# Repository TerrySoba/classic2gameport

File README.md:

Classic2Gameport
================

About
-----
Classic2Gameport is an adapter that allows to connect up to two [Nintendo Wii Classic Controllers](https://en.wikipedia.org/wiki/Classic_Controller) to [PC Gameports](https://en.wikipedia.org/wiki/Game_port).
The adapter acts like a Gravis Gamepad.

Supported Devices
-----------------

The following Nintendo controllers are supported:
 * Classic Controller
 * Classic Controler Pro
 * SNES Mini Controller

The PC needs to have a Gameport to use this adapter.

Adapter Modes
-------------

| Mode | Combination | Description |
|------|-------------|--|
| Normal Mode | SELECT + DOWN | Button B -> 1<br>Button Y -> 2<br>Button A -> 3<br>Button X -> 4 |
| Two Player Mode | (connect two controllers) | Button B1 -> 1<br>Button Y1 -> 2<br>Button B2 -> 3<br>Button Y2 -> 4<br>
| Jump'n'Run Mode | SELECT + UP | Button Y -> 1<br>Button A -> 2<br>Button B -> Up |

Building Instructions
---------------------

Here are some images of the assembled adapter:

The Kicad files of the PCB can be found in the pcb directory of the repository.

The firmware for the ST STM32G071KxT microcontroller can be found in the firmware directory.

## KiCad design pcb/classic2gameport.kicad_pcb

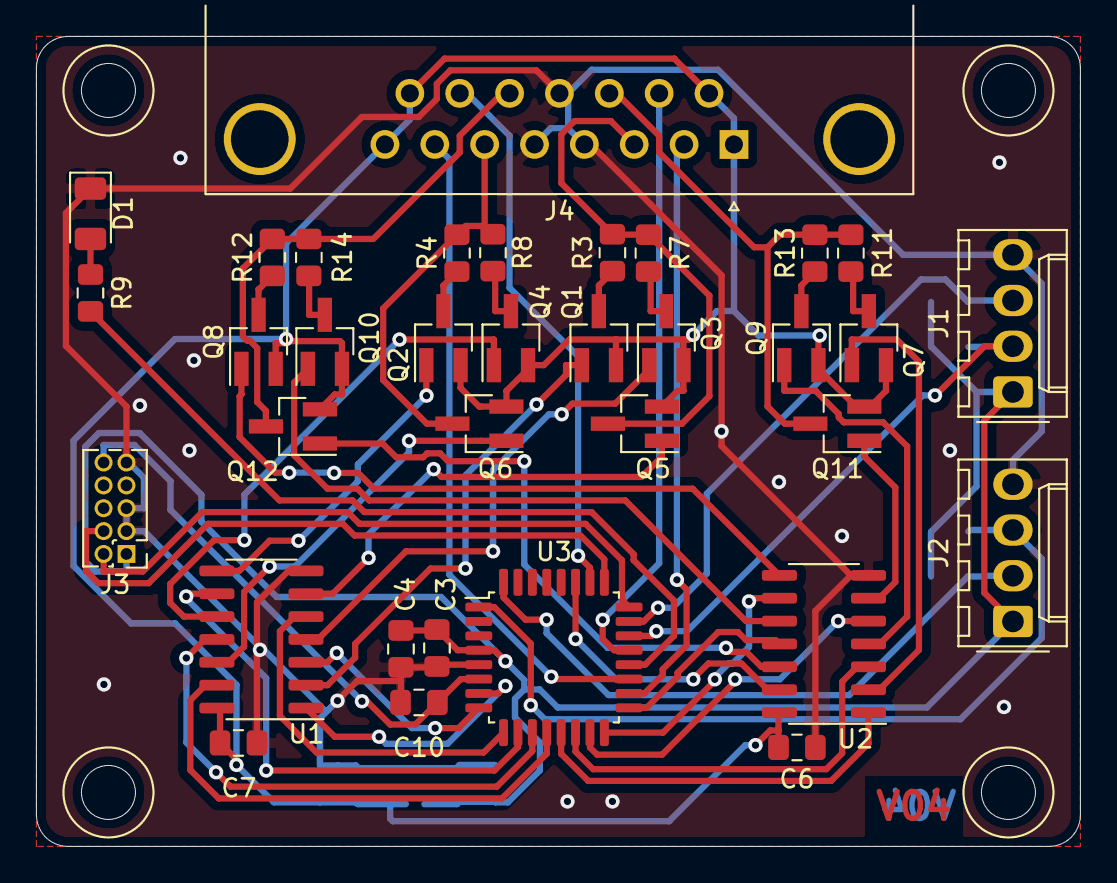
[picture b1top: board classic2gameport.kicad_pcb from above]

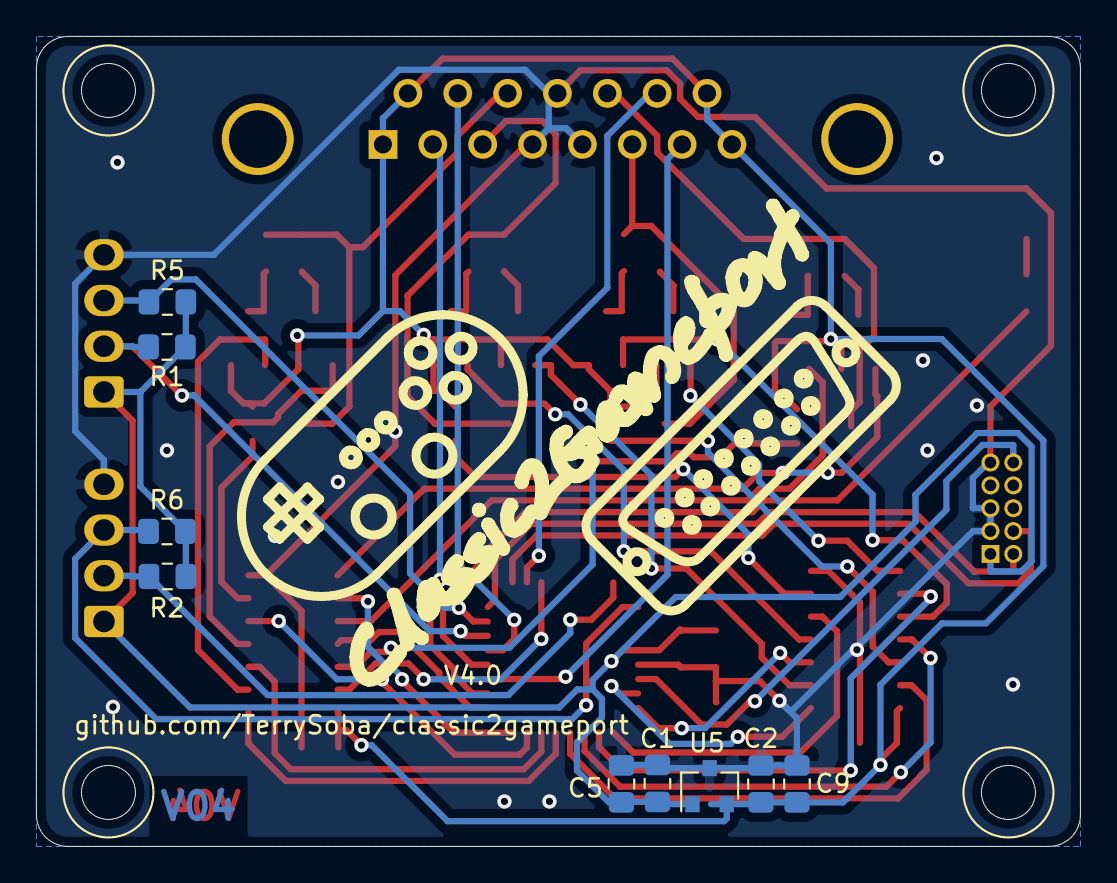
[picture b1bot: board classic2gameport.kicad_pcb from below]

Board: 2 copper layers, 58.0 x 45.0 mm, 43 parts (9 on the bottom side), 52 nets.

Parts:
C1, C2, C3, C6, C7, C10: 100nF; C_0805_2012Metric_Pad1.15x1.40mm_HandSolder
C4: 1µF; C_0805_2012Metric_Pad1.15x1.40mm_HandSolder
C5, C9: 4.7µF; C_0805_2012Metric_Pad1.15x1.40mm_HandSolder
D1: LED; LED_1206_3216Metric
J1, J2: Conn_01x04; Molex_KK-254_AE-6410-04A_1x04_P2.54mm_Vertical
J3: Conn_02x05_Odd_Even; PinHeader_2x05_P1.27mm_Vertical
J4: DB15_Male; DSUB-15_Male_Horizontal_P2.77x2.84mm_EdgePinOffset4.94mm_Ho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
Q1, Q2, Q3, Q4, Q5, Q6, Q7, Q8, Q9, Q10, Q11, Q12: Q_PMOS_GSD; SOT-23_Handsoldering
R1, R2, R5, R6: 1kR; R_0805_2012Metric_Pad1.15x1.40mm_HandSolder
R3, R4, R7, R8, R11, R12, R13, R14: 100kR; R_0805_2012Metric_Pad1.15x1.40mm_HandSolder
R9: 470R; R_0805_2012Metric_Pad1.15x1.40mm_HandSolder
U1, U2: 74HC14; SOIC-14_3.9x8.7mm_P1.27mm
U3: STM32G071KxT; LQFP-32_7x7mm_P0.8mm
U5: LM3480-3.3; SOT-23

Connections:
3.3V: C1.1, C3.1, C4.1, C5.1, J1.1, J2.1, J3.1, R1.1, R2.1, R5.1, R6.1, U3.4, U5.1
5V: C2.1, C6.1, C7.1, C9.1, J4.1, J4.8, J4.9, J4.15, Q1.2, Q2.2, Q3.2, Q4.2, Q5.2, Q6.2, Q7.2, Q8.2, Q9.2, Q10.2, Q11.2, Q12.2, U1.14, U2.14, U5.2
BUTTON1: J4.2, U3.18
BUTTON2: J4.7, U3.19
BUTTON3: J4.10, U3.21
BUTTON4: J4.14, U3.26
GND: C1.2, C2.2, C3.2, C4.2, C5.2, C6.2, C7.2, C9.2, C10.2, D1.1, J1.4, J2.4, J3.3, J3.5, J3.9, J4.4, J4.5, J4.12, U1.7, U2.7, U3.5, U5.3
JS1_X1: U1.1, U3.7
JS1_X2: U1.3, U3.8
JS1_X3: U1.5, U3.9
JS1_X_AXIS: J4.3, Q5.3, R3.2, R7.2
JS1_Y1: U1.9, U3.10
JS1_Y2: U1.11, U3.11
JS1_Y3: U1.13, U3.12
JS1_Y_AXIS: J4.6, Q6.3, R4.2, R8.2
JS2_X1: U2.1, U3.13
JS2_X2: U2.3, U3.14
JS2_X3: U2.5, U3.15
JS2_X_AXIS: J4.11, Q11.3, R11.2, R13.2
JS2_Y1: U2.9, U3.16
JS2_Y2: U2.11, U3.17
JS2_Y3: U2.13, U3.27
JS2_Y_AXIS: J4.13, Q12.3, R12.2, R14.2
NRST: C10.1, J3.10, U3.6
unnamed: D1.2, R9.2
unnamed: Q1.1, U1.2
unnamed: Q1.3, R3.1
unnamed: Q2.1, U1.8
unnamed: Q2.3, R4.1
unnamed: Q3.1, U1.4
unnamed: Q3.3, R7.1
unnamed: Q4.1, U1.10
unnamed: Q4.3, R8.1
unnamed: Q5.1, U1.6
unnamed: Q6.1, U1.12
unnamed: Q7.1, U2.2
unnamed: Q7.3, R11.1
unnamed: Q8.1, U2.8
unnamed: Q8.3, R12.1
unnamed: Q9.1, U2.4
unnamed: Q9.3, R13.1
unnamed: Q10.1, U2.10
unnamed: Q10.3, R14.1
unnamed: Q11.1, U2.6
unnamed: Q12.1, U2.12
unnamed: R9.1, U3.20
SCL: J2.2, R2.2, U3.32
SCL2: J1.2, R1.2, U3.22
SDA: J2.3, R6.2, U3.1
SDA2: J1.3, R5.2, U3.23
SWCLK: J3.4, U3.25
SWDIO: J3.2, U3.24

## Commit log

2020-05-04 Initial import
2020-05-05 Add LED
2020-05-05 Add (incomplete) BOM
2020-05-06 Slightly change layout
2020-05-07 Add BOM
2020-05-08 Add firmware
2020-05-10 Change some footprints
2020-05-12 Add gitignore
2020-05-12 Remove obsolete code
2020-05-14 Finish firmware
2020-05-17 Add readme
2020-05-17 Fix readme
2020-05-23 Change to STM32 MCU
2020-05-23 Redesign again
2020-06-01 Change firmware to STM32
2020-06-01 Fix PCB
2020-06-04 Version 4.0 of PCB
2020-06-04 Fix silkscreen
2020-06-25 Intermediate state
2020-06-25 Change MCU to STM32G071KB
2020-06-25 Support 2nd joystick axis
2020-06-26 Support 2nd classic controller
2020-07-02 Allow mapping of buttons
2020-07-04 If controller is not connected disconnect gameport axis
2020-07-04 Change order of ButtonMap
2020-07-04 Implement jump and run mode
2020-07-04 Add some images of the adapter
2020-07-05 Add image of finished adapter
2020-07-06 Add digikey numbers to BOM
